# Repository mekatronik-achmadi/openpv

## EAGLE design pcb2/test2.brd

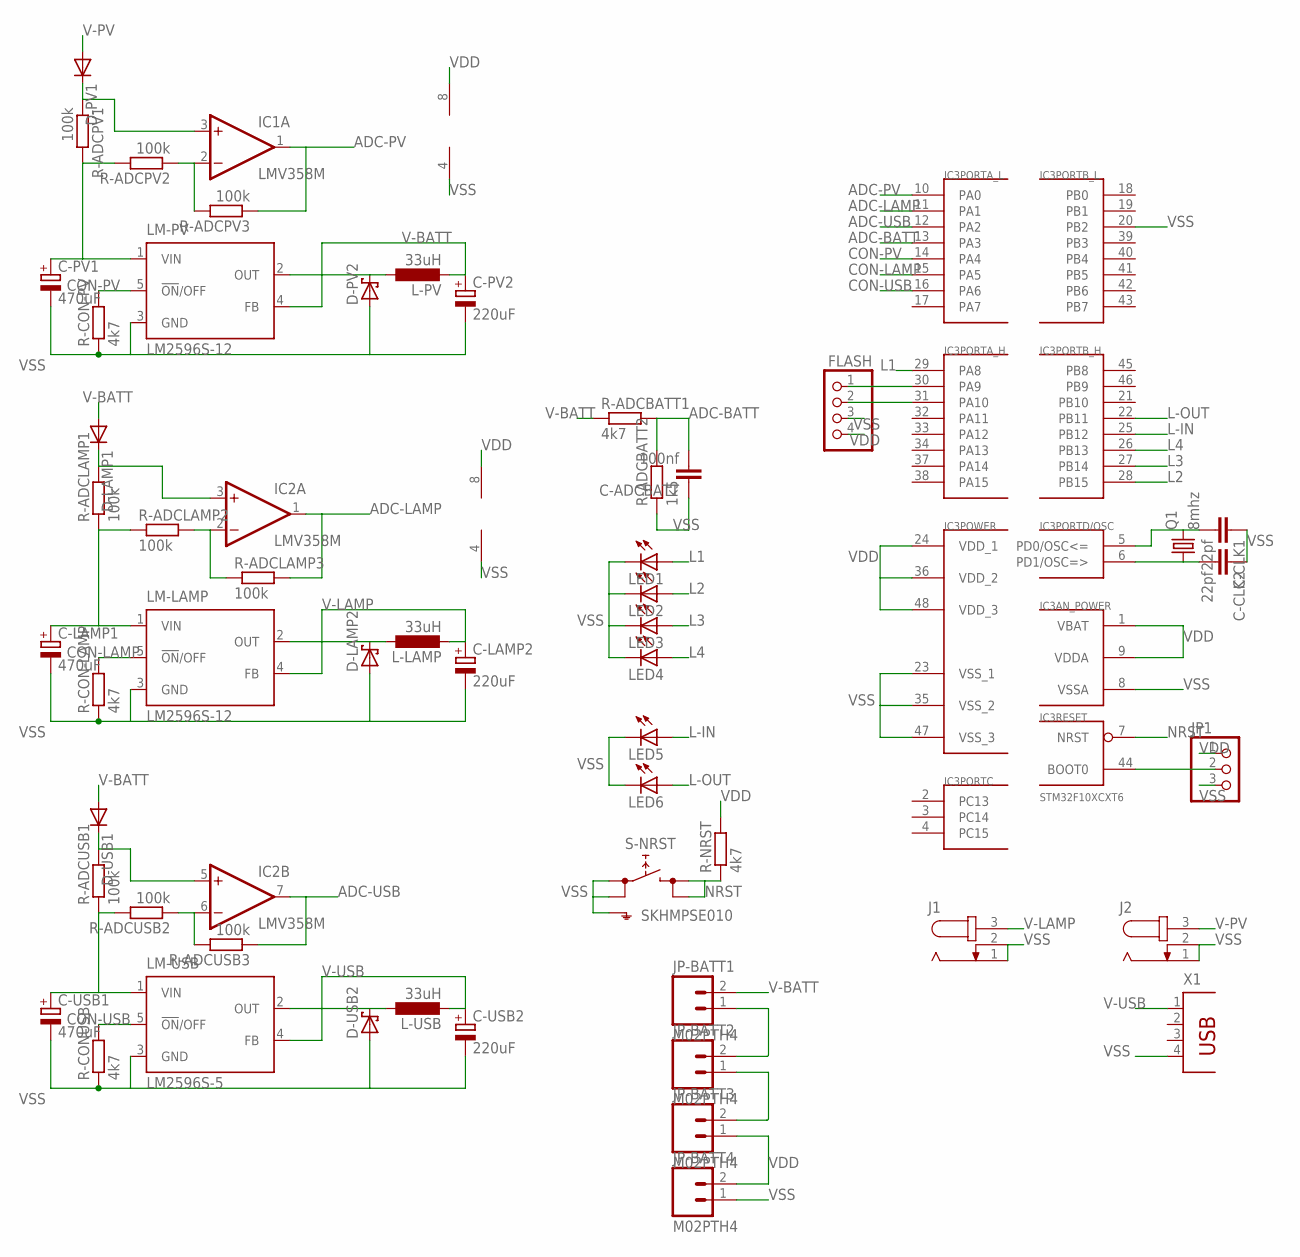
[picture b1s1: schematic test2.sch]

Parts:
C-ADCBATT: 100nf; C0805
C-CLK1, C-CLK2: 22pf; C0805
C-LAMP1: 470uF; E2,5-5
C-LAMP2: 220uF; E2,5-5
C-PV1: 470uF; E2,5-5
C-PV2: 220uF; E2,5-5
C-USB1: 470uF; E2,5-5
C-USB2: 220uF; E2,5-5
D-LAMP1: DIODE-DO-214AC; DO-214AC
D-LAMP2: SCHOTTKY-DIODE; DIODE_SMB
D-PV1: DIODE-DO-214AC; DO-214AC
D-PV2: SCHOTTKY-DIODE; DIODE_SMB
D-USB1: DIODE-DO-214AC; DO-214AC
D-USB2: SCHOTTKY-DIODE; DIODE_SMB
FLASH: PINHD-1X4; 1X04
IC1, IC2: LMV358M; SO08
IC3: STM32F10XCXT6; TQFP48
J1, J2: JACK-PLUG0; SPC4077
JP1: PINHD-1X3; 1X03
JP-BATT1, JP-BATT2, JP-BATT3, JP-BATT4: M02PTH4; 1X02_XTRA_BIG
L-LAMP: 33uH; POWER-CHOKE_WE-TPC
L-PV: 33uH; POWER-CHOKE_WE-TPC
L-USB: 33uH; POWER-CHOKE_WE-TPC
LED1, LED2, LED3, LED4, LED5, LED6: LEDCHIP-LED0805; CHIP-LED0805
LM-LAMP: LM2596S-12; TO263-5
LM-PV: LM2596S-12; TO263-5
LM-USB: LM2596S-5; TO263-5
Q1: 8mhz; HC49/S
R-ADCBATT1: 4k7; R0805
R-ADCBATT2: 1k5; R0805
R-ADCLAMP1, R-ADCLAMP2, R-ADCLAMP3: 100k; R0805
R-ADCPV1, R-ADCPV2, R-ADCPV3: 100k; R0805
R-ADCUSB1, R-ADCUSB2, R-ADCUSB3: 100k; R0805
R-CON-LAMP: 4k7; R0805
R-CON-PV: 4k7; R0805
R-CONUSB: 4k7; R0805
R-NRST: 4k7; R0805
S-NRST: SKHMPSE010; SKHMPXE010
X1: PN87520

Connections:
ADC-BATT: C-ADCBATT.2, IC3.13 (PA3), R-ADCBATT1.2, R-ADCBATT2.2
ADC-LAMP: IC2.1 (OUT), IC3.11 (PA1), R-ADCLAMP3.2
ADC-PV: IC1.1 (OUT), IC3.10 (PA0), R-ADCPV3.1
ADC-USB: IC2.7 (OUT), IC3.12 (PA2), R-ADCUSB3.1
CON-LAMP: IC3.15 (PA5), LM-LAMP.5 (!ON!/OFF), R-CON-LAMP.2
CON-PV: IC3.14 (PA4), LM-PV.5 (!ON!/OFF), R-CON-PV.2
CON-USB: IC3.16 (PA6), LM-USB.5 (!ON!/OFF), R-CONUSB.2
L1: IC3.29 (PA8), LED1.A
L2: IC3.28 (PB15), LED2.A
L3: IC3.27 (PB14), LED3.A
L4: IC3.26 (PB13), LED4.A
L-IN: IC3.25 (PB12), LED5.A
L-OUT: IC3.22 (PB11), LED6.A
unnamed: D-PV2.C (A), L-PV.1, LM-PV.2 (OUT)
unnamed: D-LAMP2.C (A), L-LAMP.1, LM-LAMP.2 (OUT)
unnamed: D-USB2.C (A), L-USB.1, LM-USB.2 (OUT)
unnamed: IC2.2 (-IN), R-ADCLAMP2.2, R-ADCLAMP3.1
unnamed: C-USB1.+, LM-USB.1 (VIN), R-ADCUSB1.1, R-ADCUSB2.2
unnamed: C-CLK2.2, IC3.6 (PD1/OSC=>), Q1.1
unnamed: C-LAMP1.+, LM-LAMP.1 (VIN), R-ADCLAMP1.1, R-ADCLAMP2.1
unnamed: D-LAMP1.C, IC2.3 (+IN), R-ADCLAMP1.2
unnamed: IC1.2 (-IN), R-ADCPV2.1, R-ADCPV3.2
unnamed: C-PV1.+, LM-PV.1 (VIN), R-ADCPV1.2, R-ADCPV2.2
unnamed: D-PV1.C, IC1.3 (+IN), R-ADCPV1.1
unnamed: IC3.44 (BOOT0), JP1.2
unnamed: C-CLK1.2, IC3.5 (PD0/OSC<=), Q1.2
unnamed: IC2.6 (-IN), R-ADCUSB2.1, R-ADCUSB3.2
unnamed: D-USB1.C, IC2.5 (+IN), R-ADCUSB1.2
unnamed: FLASH.2, IC3.31 (PA10)
unnamed: FLASH.1, IC3.30 (PA9)
unnamed: JP-BATT2.1, JP-BATT3.2
unnamed: JP-BATT1.1, JP-BATT2.2
NRST: IC3.7 (NRST), R-NRST.1, S-NRST.3 (2.1), S-NRST.4 (2.2)
V-BATT: C-PV2.+, D-LAMP1.A, D-USB1.A, JP-BATT1.2, L-PV.2, LM-PV.4 (FB), R-ADCBATT1.1
V-LAMP: C-LAMP2.+, J1.3, L-LAMP.2, LM-LAMP.4 (FB)
V-PV: D-PV1.A, J2.3
V-USB: C-USB2.+, L-USB.2, LM-USB.4 (FB), X1.1
VDD: FLASH.4, IC1.8 (V+), IC2.8 (V+), IC3.1 (VBAT), IC3.9 (VDDA), IC3.24 (VDD_1), IC3.36 (VDD_2), IC3.48 (VDD_3), JP1.1, JP-BATT3.1, JP-BATT4.2, R-NRST.2
VSS: C-ADCBATT.1, C-CLK1.1, C-CLK2.1, C-LAMP1.-, C-LAMP2.-, C-PV1.-, C-PV2.-, C-USB1.-, C-USB2.-, D-LAMP2.A (C), D-PV2.A (C), D-USB2.A (C), FLASH.3, IC1.4 (V-), IC2.4 (V-), IC3.8 (VSSA), IC3.20 (PB2), IC3.23 (VSS_1), IC3.35 (VSS_2), IC3.47 (VSS_3), J1.1, J1.2, J2.1, J2.2, JP1.3, JP-BATT4.1, LED1.C, LED2.C, LED3.C, LED4.C, LED5.C, LED6.C, LM-LAMP.3 (GND), LM-PV.3 (GND), LM-USB.3 (GND), R-ADCBATT2.1, R-CON-LAMP.1, R-CON-PV.1, R-CONUSB.1, S-NRST.1 (1.1), S-NRST.2 (1.2), S-NRST.5 (SH), X1.4

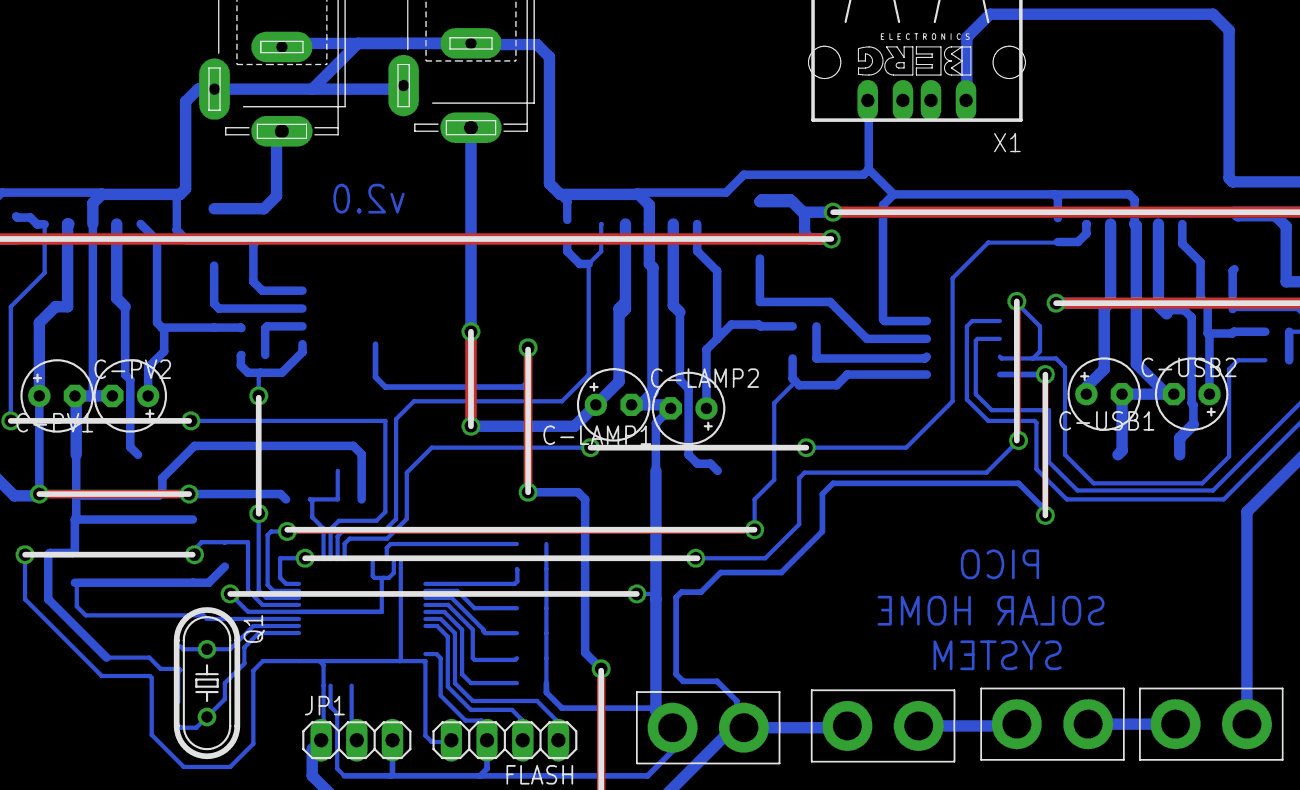
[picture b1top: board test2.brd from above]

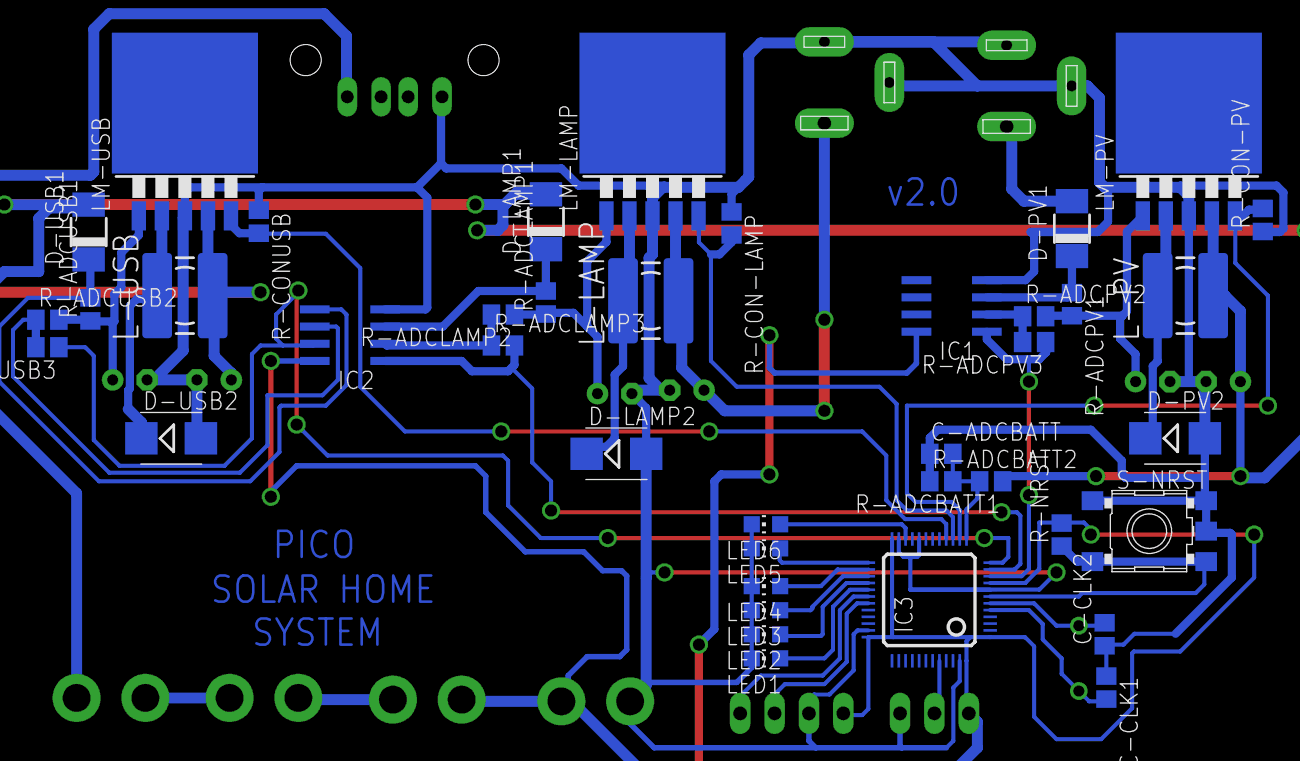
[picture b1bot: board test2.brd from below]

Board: 2 copper layers, 56 parts (40 on the bottom side), 39 nets.

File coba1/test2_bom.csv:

Qty,Buy,Value,Device,Package,TOKO,URL,KODE,SATUAN,HARGA
2,2,,JACK-PLUG0,SPC4077,Berkat Keputih,-,-,"Rp1,500.00","Rp3,000.00"
1,1,,PINHD-1X3,1X03,Berkat Keputih,-,-,"Rp4,000.00","Rp4,000.00"
1,0,,PINHD-1X4,1X04,Berkat Keputih,-,-,"Rp4,000.00",Rp0.00
1,1,,PN87520,PN87520,Berkat Keputih,-,-,"Rp3,500.00","Rp3,500.00"
3,10,220uF,CPOL-EUE2.5-5,"E2,5-5",Berkat Keputih,-,-,Rp500.00,"Rp5,000.00"
3,5,470uF,CPOL-EUE2.5-5,"E2,5-5",Berkat Keputih,-,-,Rp500.00,"Rp2,500.00"
1,1,8mhz,CRYSTALHC49S,HC49/S,Berkat Keputih,-,-,"Rp4,000.00","Rp4,000.00"
4,4,M02PTH4,M02PTH4,1X02_XTRA_BIG,Berkat Keputih,-,-,"Rp1,500.00","Rp6,000.00"
1,2,PCB,PCB,Circuit Board,CV.MPI,-,-,"Rp75,000.00","Rp150,000.00"
1,10,1k5,R-EU_R0805,R0805,Digiware Bratang,http://digiwarestore.com/en/smd-0805/15k-ohm-0805-510-pcs-pe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,915-015,Rp100.00,"Rp1,000.00"
3,5,,SCHOTTKY-DIODE,DIODE_SMB,Lapantech Bratang,http://lapantech.com/Dioda/Dioda-1n5819-SMD,DIO0078,Rp500.00,"Rp2,500.00"
3,4,,DIODE-DO-214AC,DO-214AC,SFE MALANG,http://sfe-electronics.com/diode/883-ss34-3a-smd-diode.html,DR02002,"Rp1,500.00","Rp6,000.00"
6,10,,LEDCHIP-LED0805,CHIP-LED0805,SFE MALANG,http://sfe-electronics.com/display/1384-smd0805-red-led.html,LED0302001,Rp500.00,"Rp5,000.00"
9,10,100k,R-EU_R0805,R0805,SFE MALANG,http://sfe-electronics.com/resistor/643-100k-ohm-smd0805-res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,R010203042,Rp50.00,Rp500.00
1,10,100nf,C-EUC0805,C0805,SFE MALANG,http://sfe-electronics.com/capacitor/130-150nf-smd0805-capac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,C010203033,Rp75.00,Rp750.00
2,10,22pf,C-EUC0805,C0805,SFE MALANG,http://sfe-electronics.com/capacitor/107-22pf-smd0805-capaci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,C010203009,Rp75.00,Rp750.00
3,5,33uH,L-EUWE-TPC,POWER-CHOKE_WE-TPC,SFE MALANG,http://sfe-electronics.com/inductor/846-33uh-power-inductor-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,L0206003,"Rp3,500.00","Rp17,500.00"
5,10,4k7,R-EU_R0805,R0805,SFE MALANG,http://sfe-electronics.com/resistor/629-47k-ohm-smd0805-resi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,R010203028,Rp50.00,Rp500.00
2,3,LM2596S-12,LM2596S,TO263-5,SFE MALANG,http://sfe-electronics.com/integrated-circuit/1738-lm2596s-12.html,ICVR02020,"Rp15,000.00","Rp45,000.00"
1,2,LM2596S-5,LM2596S,TO263-5,SFE MALANG,http://sfe-electronics.com/integrated-circuit/918-lm2596s-50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,ICVR02016,"Rp10,000.00","Rp20,000.00"
2,3,LMV358M,LMV358M,SO08,SFE MALANG,http://sfe-electronics.com/integrated-circuit/933-lmv358idgk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,ICOP02001,"Rp3,500.00","Rp10,500.00"
1,2,SKHMPSE010,SKHMPSE010,SKHMPXE010,SFE MALANG,http://sfe-electronics.com/switch-and-keypad/1436-6mmx6mm-sm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,TS02001,"Rp1,000.00","Rp2,000.00"
1,2,STM32F10XCXT6,STM32F10XCXT6,TQFP48,SFE MALANG,http://sfe-electronics.com/microcontroller-ic/2488-stm32f100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,ICMC020102004,"Rp30,000.00","Rp60,000.00"
,,,,,,,,,
,Total,"Rp350,000.00",,,,,,,
,Bulat,"Rp400,000.00",,,,,,,

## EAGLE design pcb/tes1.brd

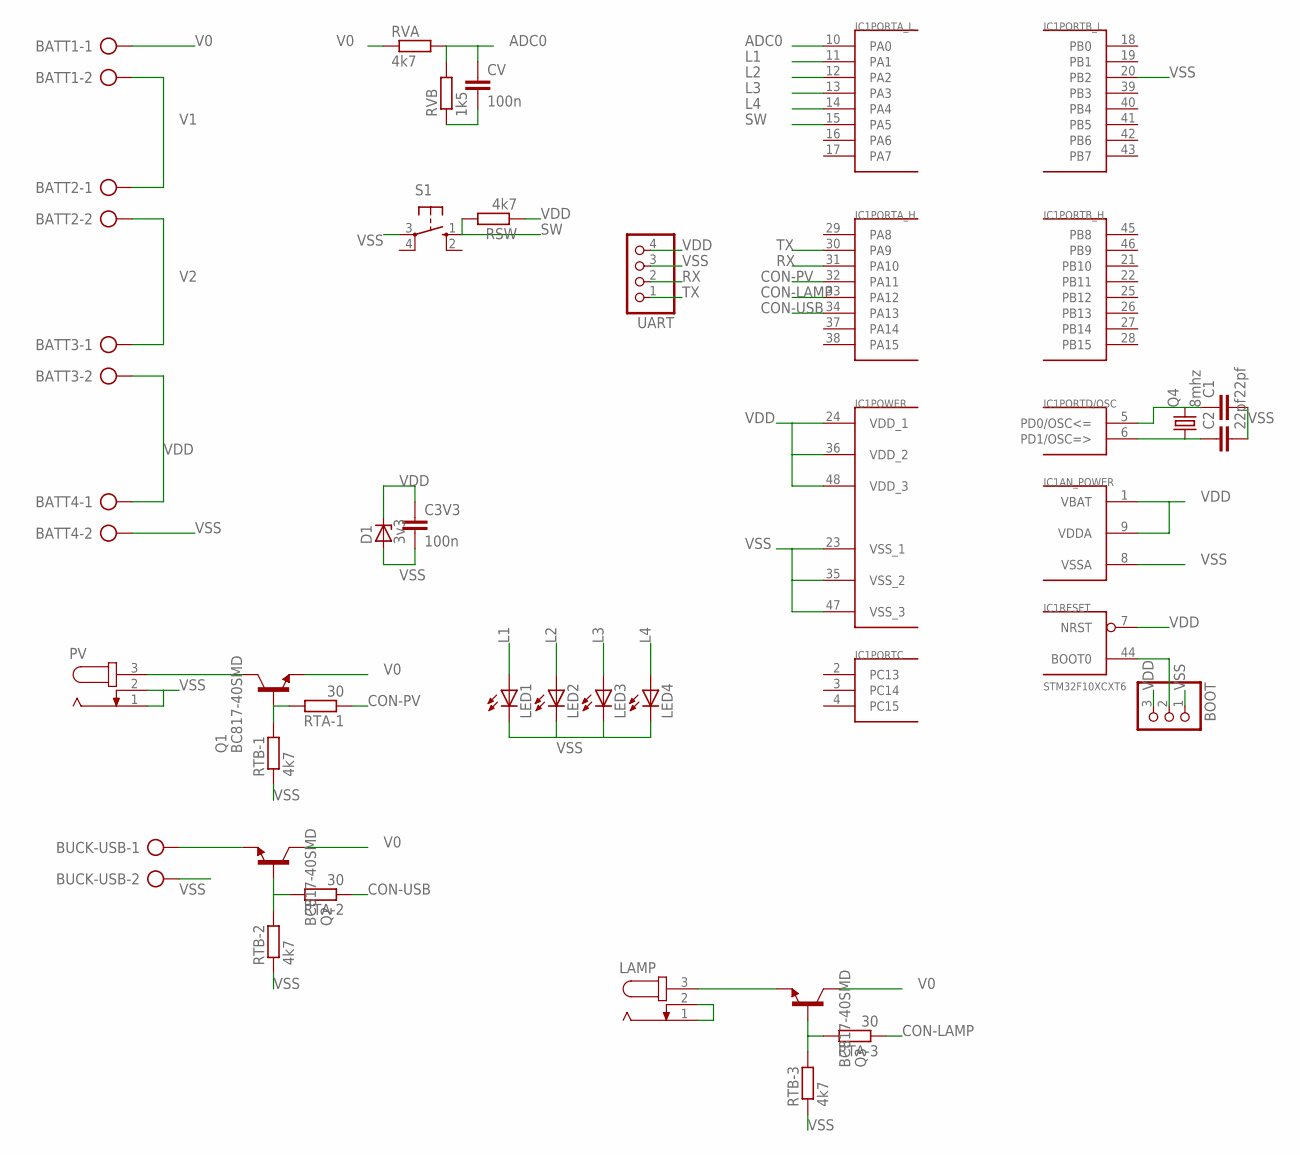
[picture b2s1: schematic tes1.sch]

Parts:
BATT1, BATT2, BATT3, BATT4: AK300/2
BOOT: PINHD-1X3; 1X03
BUCK-USB: AK300/2
C1, C2: 22pf; C0805
C3V3: 100n; C0805
CV: 100n; C0805
D1: 3v3; SMB
IC1: STM32F10XCXT6; TQFP48
LAMP: JACK-PLUG0; SPC4077
LED1, LED2, LED3, LED4: LEDCHIP-LED0805; CHIP-LED0805
PV: JACK-PLUG0; SPC4077
Q1, Q2, Q3: BC817-40SMD; SOT23-BEC
Q4: 8mhz; HC49U-V
RSW: 4k7; R0805
RTA-1, RTA-2, RTA-3: 30; R0805
RTB-1, RTB-2, RTB-3: 4k7; R0805
RVA: 4k7; R0805
RVB: 1k5; R0805
S1: 10-XX; B3F-10XX
UART: PINHD-1X4; 1X04

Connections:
ADC0: CV.1, IC1.10 (PA0), RVA.2, RVB.2
CON-LAMP: IC1.33 (PA12), RTA-3.1
CON-PV: IC1.32 (PA11), RTA-1.1
CON-USB: IC1.34 (PA13), RTA-2.1
L1: IC1.11 (PA1), LED1.A
L2: IC1.12 (PA2), LED2.A
L3: IC1.13 (PA3), LED3.A
L4: IC1.14 (PA4), LED4.A
unnamed: PV.3, Q1.C
unnamed: LAMP.3, Q3.E
unnamed: Q1.B, RTA-1.2, RTB-1.2
unnamed: Q3.B, RTA-3.2, RTB-3.2
unnamed: BOOT.2, IC1.44 (BOOT0)
unnamed: BUCK-USB.1, Q2.E
unnamed: Q2.B, RTA-2.2, RTB-2.2
unnamed: C2.1, IC1.6 (PD1/OSC=>), Q4.1
unnamed: C1.1, IC1.5 (PD0/OSC<=), Q4.2
RX: IC1.31 (PA10), UART.2
SW: IC1.15 (PA5), RSW.2, S1.1 (S)
TX: IC1.30 (PA9), UART.1
V0: BATT1.1, Q1.E, Q2.C, Q3.C, RVA.1
V1: BATT1.2, BATT2.1
V2: BATT2.2, BATT3.1
VDD: BATT3.2, BATT4.1, BOOT.3, C3V3.1, D1.C, IC1.1 (VBAT), IC1.7 (NRST), IC1.9 (VDDA), IC1.24 (VDD_1), IC1.36 (VDD_2), IC1.48 (VDD_3), RSW.1, UART.4
VSS: BATT4.2, BOOT.1, BUCK-USB.2, C1.2, C2.2, C3V3.2, CV.2, D1.A, IC1.8 (VSSA), IC1.20 (PB2), IC1.23 (VSS_1), IC1.35 (VSS_2), IC1.47 (VSS_3), LAMP.1, LAMP.2, LED1.C, LED2.C, LED3.C, LED4.C, PV.1, PV.2, RTB-1.1, RTB-2.1, RTB-3.1, RVB.1, S1.3, UART.3

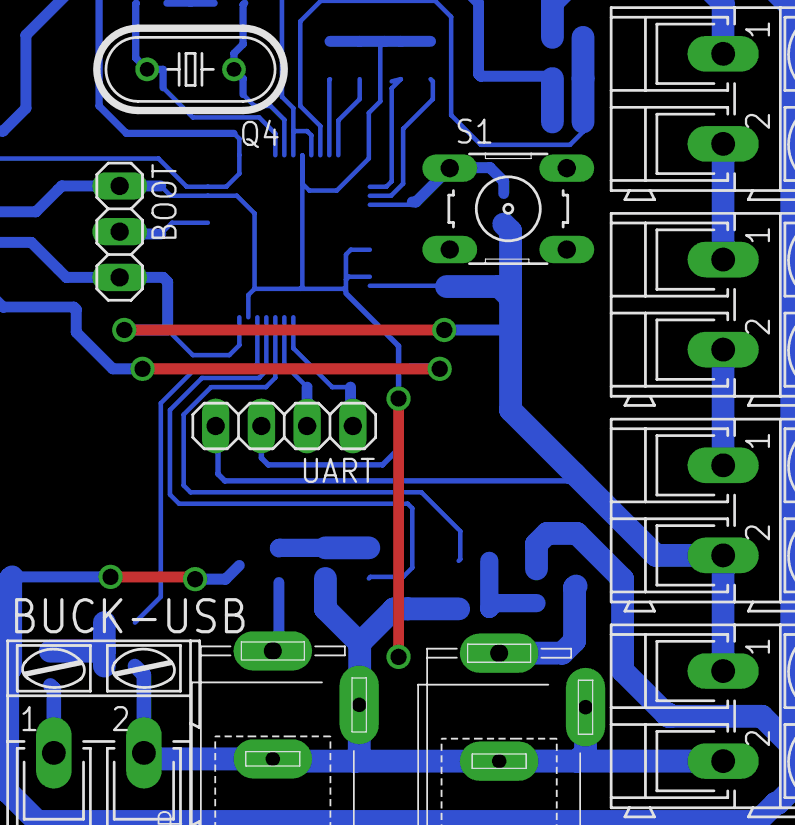
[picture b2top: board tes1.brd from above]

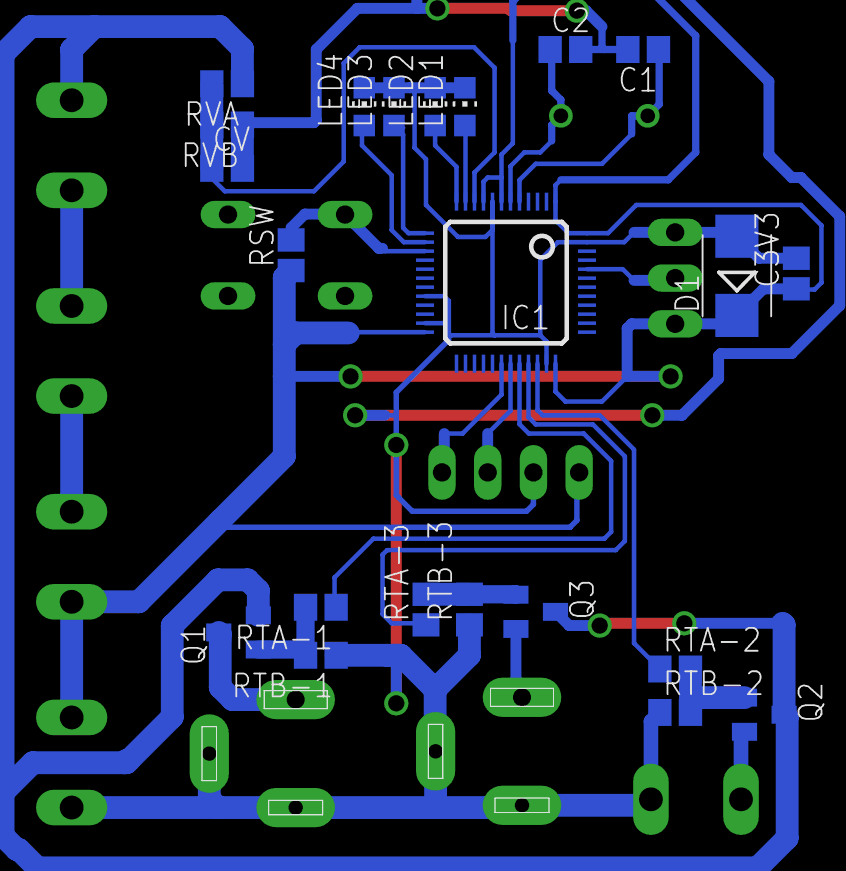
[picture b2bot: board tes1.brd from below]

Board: 2 copper layers, 33 parts (22 on the bottom side), 25 nets.

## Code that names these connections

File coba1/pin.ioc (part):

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Mcu.Name=STM32F100C(8-B)Tx
Mcu.Package=LQFP48
PA0-WKUP.Mode=IN0
PA0-WKUP.Signal=ADC1_IN0
PA1.Mode=IN1
PA1.Signal=ADC1_IN1
PA10.Mode=Asynchronous
PA10.Signal=USART1_RX
PA2.Mode=IN2
PA2.Signal=ADC1_IN2
PA3.Mode=IN3
PA3.Signal=ADC1_IN3
PA4.Signal=GPIO_Output
PA5.Signal=GPIO_Output
PA6.Signal=GPIO_Output
PA8.Signal=GPIO_Output
PA9.Mode=Asynchronous
PA9.Signal=USART1_TX
PB11.Signal=GPIO_Output
PB12.Signal=GPIO_Output
PB13.Signal=GPIO_Output
PB14.Signal=GPIO_Output
PB15.Signal=GPIO_Output
PB2.Mode=Event-Out
PB2.Signal=CORTEX_EVENT_OUT

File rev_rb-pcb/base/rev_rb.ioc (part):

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Mcu.Name=STM32F103R(8-B)Tx
Mcu.Package=LQFP64
PA0-WKUP.Mode=IN0
PA0-WKUP.Signal=ADC1_IN0
PA1.Mode=IN1
PA1.Signal=ADC1_IN1
PA10.Mode=Asynchronous
PA10.Signal=USART1_RX
PA2.Mode=IN2
PA2.Signal=ADC1_IN2
PA3.Mode=IN3
PA3.Signal=ADC1_IN3
PA4.Mode=IN4
PA4.Signal=ADC1_IN4
PA5.Mode=IN5
PA5.Signal=ADC1_IN5
PA6.Mode=IN6
PA6.Signal=ADC1_IN6
PA7.Mode=IN7
PA7.Signal=ADC1_IN7
PA9.Mode=Asynchronous
PA9.Signal=USART1_TX
PB12.Signal=GPIO_Output
PB13.Signal=GPIO_Output
PB14.Signal=GPIO_Output
PB15.Signal=GPIO_Input
PB2.Mode=Event-Out
PB2.Signal=CORTEX_EVENT_OUT
PB3.Signal=GPIO_Output
PB4.Signal=GPIO_Output
PB5.Signal=GPIO_Output
PB6.Signal=GPIO_Output
PB7.Signal=GPIO_Output
PB8.Signal=GPIO_Output
PB9.Signal=GPIO_Output
PC14-OSC32_IN.Mode=LSE-External-Oscillator
PC14-OSC32_IN.Signal=SYS_OSC32_IN
PC15-OSC32_OUT.Mode=LSE-External-Oscillator
PC15-OSC32_OUT.Signal=SYS_OSC32_OUT
PD0-OSC_IN.Mode=HSE-External-Oscillator
PD0-OSC_IN.Signal=SYS_OSC_IN
PD1-OSC_OUT.Mode=HSE-External-Oscillator
PD1-OSC_OUT.Signal=SYS_OSC_OUT

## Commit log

2015-05-29 Pengujian tahap 1
2015-08-05 seri 2.0
2015-08-05 ready to facturing
2015-08-06 add mount holes
2015-08-22 second devs
2015-09-02 ADC test
2015-09-02 Ready for more Test
2015-09-02 After Pull
2015-09-18 interface ready to test
2015-10-08 current monitoring
2015-10-12 ready to test
2015-10-23 drain-charge test based on voltage
2015-10-24 user serial
2015-10-24 catatan perbaikan
2015-10-27 new PCB (KiCAD standard)
2015-11-01 belum apply revisi
2015-11-02 ready to build
2015-11-05 fabricate
2015-11-19 capek coyy
2015-11-25 capeeek
2015-12-04 rilis design
2015-12-04 next:assembly manual
2015-12-04 manual book
2015-12-05 send to fabrication
2015-12-06 diplay
2015-12-14 Display Main Controller
2015-12-14 display nilai
2015-12-15 design display beres
2015-12-15 lapooor
2016-01-14 big work
2016-01-21 LED lamp use SMD 1206 Resistor
2016-01-22 revisi
2016-01-28 7 Segment On
2016-02-09 display use RTOS
2016-02-09 single data OK
2016-02-09 test sim
2016-02-12 display tinggal jam-tanggal
2016-02-17 next gen PSHS
2016-02-22 4-digit for source intensity
2016-02-22 base schematic
2016-02-23 learn sleep mode
2016-02-25 begins
2016-02-29 progress
2016-03-07 test diagram
2016-03-07 new print
2016-03-09 try again
2016-03-16 standby mode
2016-04-09 chibios cannot use stm32lib's Interrupt Handler
2016-04-09 STDLib build using Chibios's Makefile
2016-04-09 stop-run by RTC
2016-04-10 use system-wide build Makefile
2016-04-11 split API
2016-04-11 test
2016-04-16 development
2016-04-16 sial
2016-04-18 rtc ok
2016-04-18 RTC Sleep working
2016-04-18 sleep test
2016-04-19 next: baterai level
2016-04-19 all pin ok

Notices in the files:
parts and their libraries:
SparkFun-Connectors: Licensing: Creative Commons ShareAlike 4.0 International - https://creativecommons.org/licenses/by-sa/4.0
